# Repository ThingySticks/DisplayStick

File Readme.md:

Photon Display Prototyping PCB.
================================

Prototype board for Particle Photon with 3.2" (eBay) display with prototype area underneath.

See individual versions for PCB specifics.

[Available on Tindie](https://www.tindie.com/products/ThingySticks/display-stick-for-a-28-display-and-photon/)

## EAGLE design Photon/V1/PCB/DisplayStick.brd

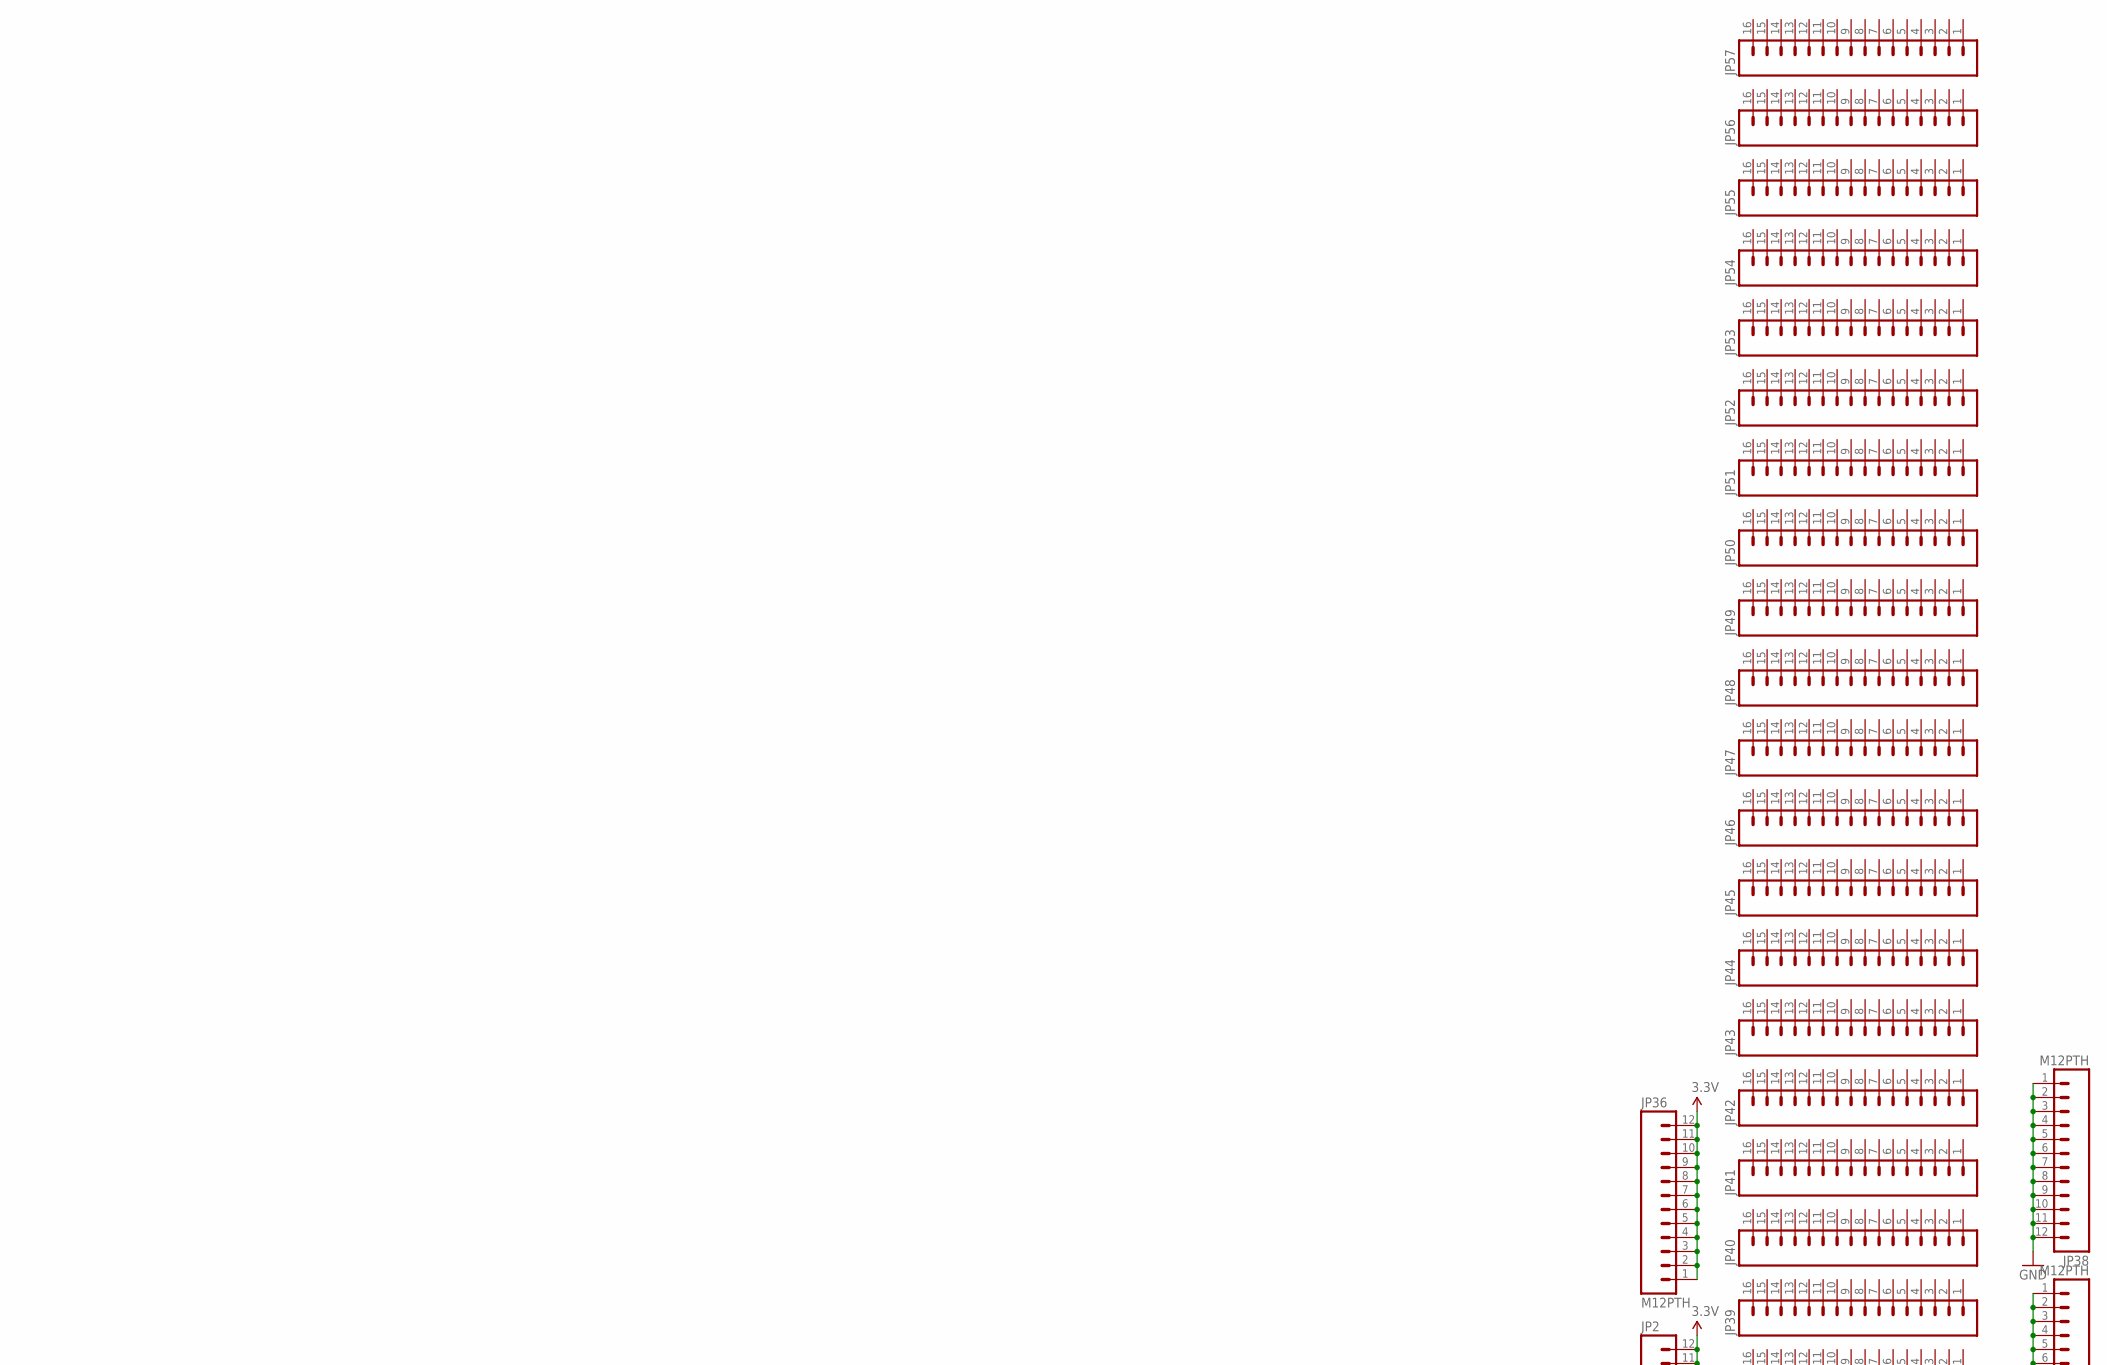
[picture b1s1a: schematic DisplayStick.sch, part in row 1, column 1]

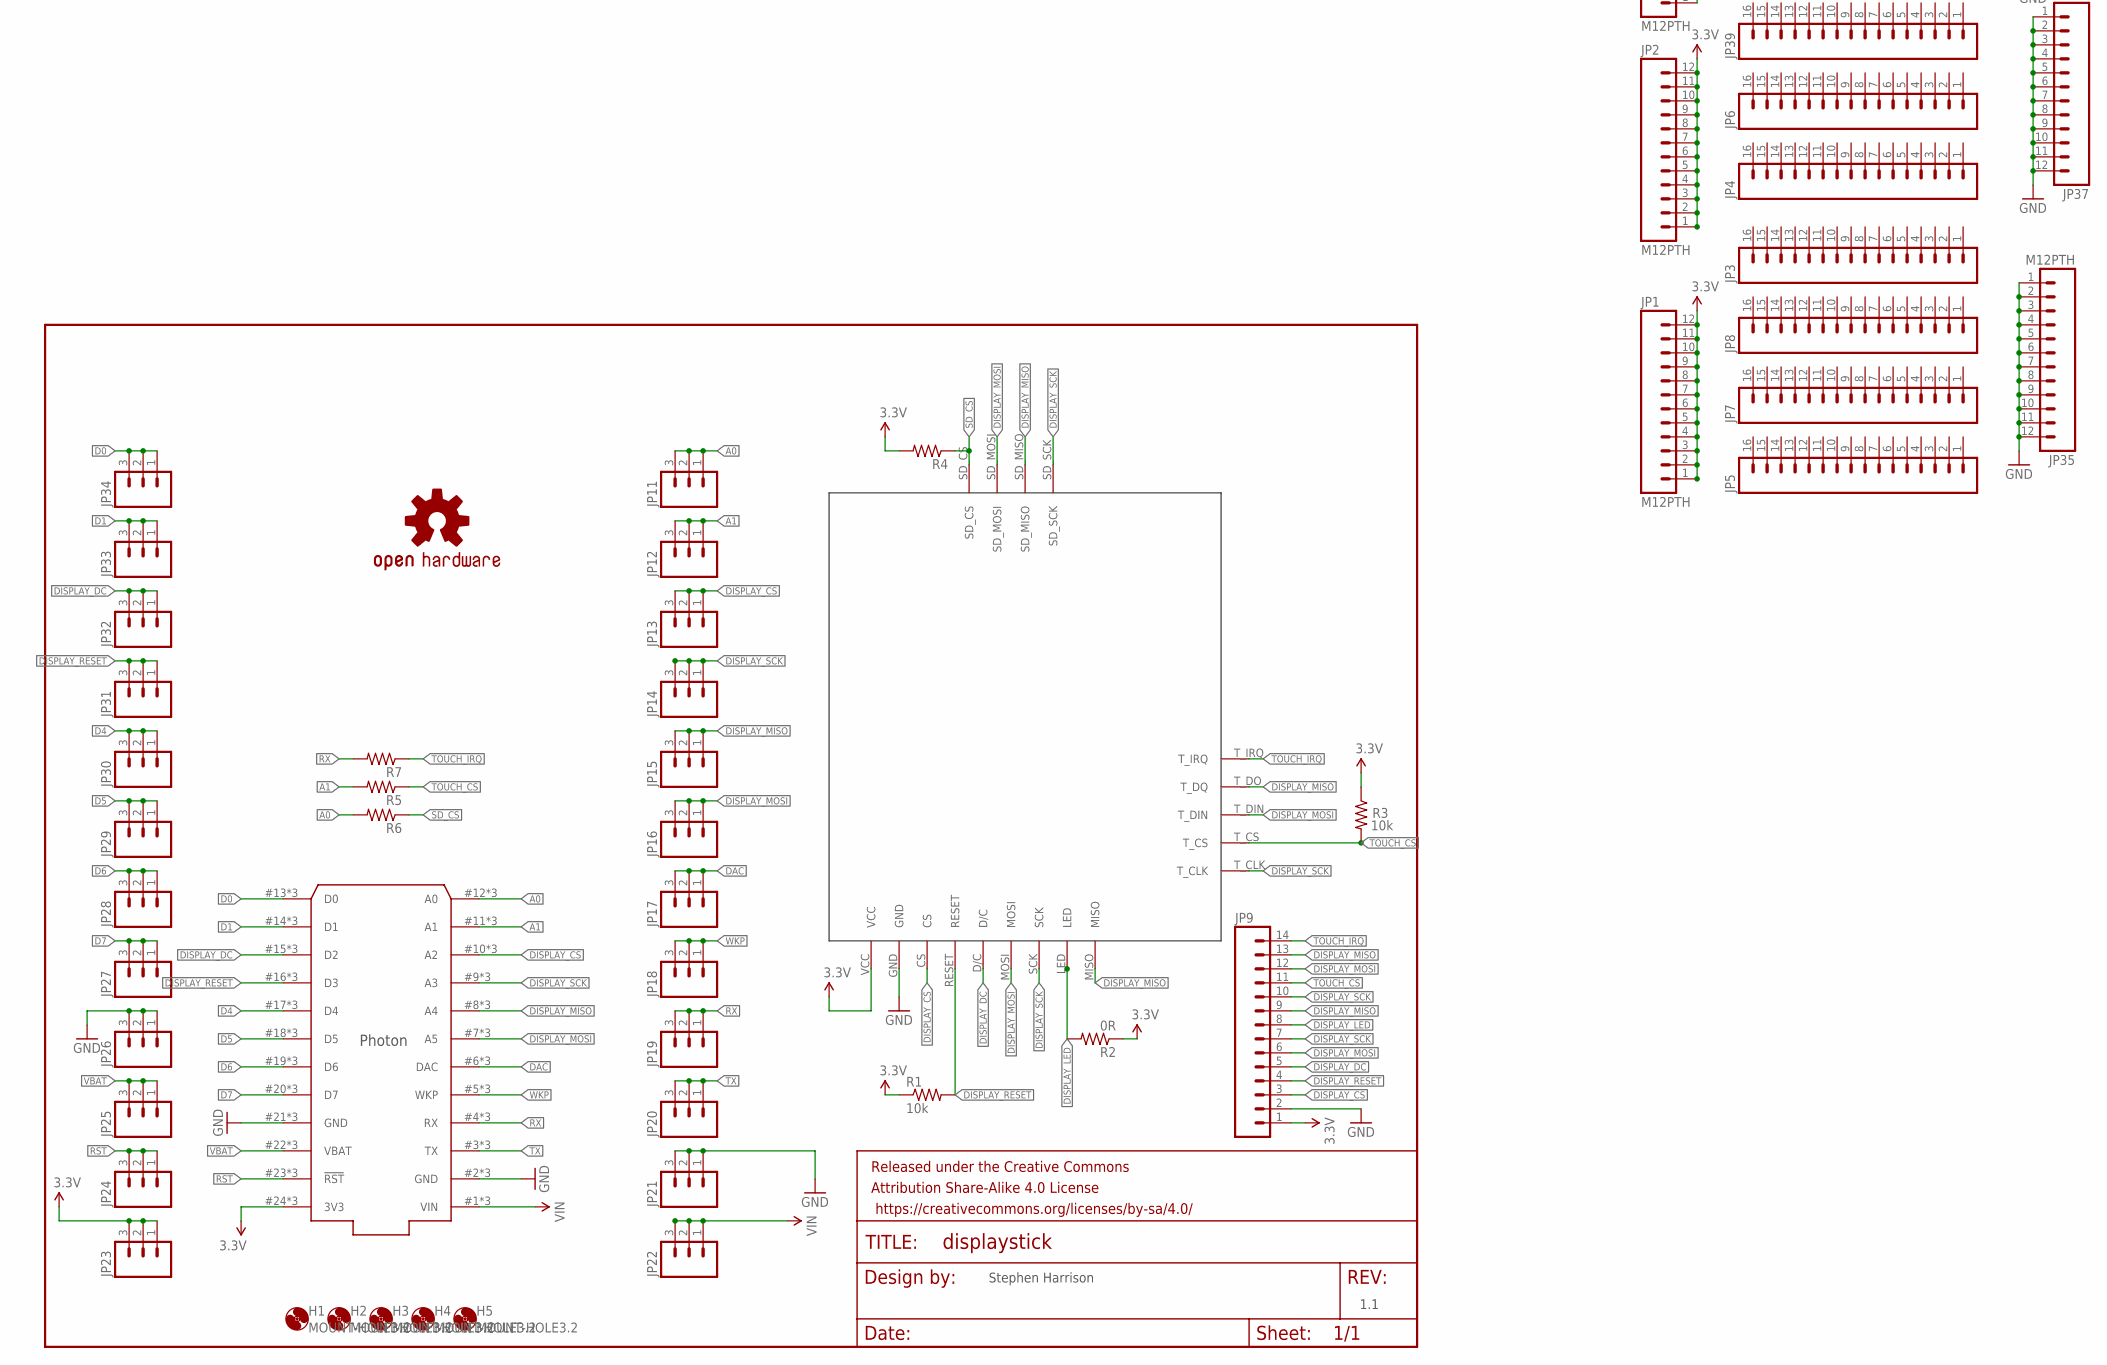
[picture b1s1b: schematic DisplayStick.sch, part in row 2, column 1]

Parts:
FRAME1: FRAME-LETTER; CREATIVE_COMMONS
H1, H2, H3, H4, H5: MOUNT-HOLE3.2; 3,2
JP1, JP2, JP35, JP36, JP37, JP38: M12PTH; 1X12-SMALL-PADS
JP3, JP4, JP5, JP6, JP7, JP8, JP39, JP40, JP41, JP42, JP43, JP44, JP45, JP46, JP47, JP48, JP49, JP50, JP51, JP52, JP53, JP54, JP55, JP56, JP57: M161X16_NO_SILK; 1X16_NO_SILK
JP9: M14; 1X14
JP11, JP12, JP13, JP14, JP15, JP16, JP17, JP18, JP19, JP20, JP21, JP22, JP23, JP24, JP25, JP26, JP27, JP28, JP29, JP30, JP31, JP32, JP33, JP34: M03PTH; 1X03
LOGO1: OSHW-LOGOL; OSHW-LOGO-L
R1, R3: 10k; 1206
R2: 0R; 1206
R4, R5, R6, R7: RESISTOR1206; 1206
U$1: TJCTM240
U$3: PHOTON_WITH_STACKABLE_HEADERS; PHOTON_STACKABLE

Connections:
3.3V: JP1.1, JP1.2, JP1.3, JP1.4, JP1.5, JP1.6, JP1.7, JP1.8, JP1.9, JP1.10, JP1.11, JP1.12, JP2.1, JP2.2, JP2.3, JP2.4, JP2.5, JP2.6, JP2.7, JP2.8, JP2.9, JP2.10, JP2.11, JP2.12, JP9.1, JP23.1, JP23.2, JP23.3, JP36.1, JP36.2, JP36.3, JP36.4, JP36.5, JP36.6, JP36.7, JP36.8, JP36.9, JP36.10, JP36.11, JP36.12, R1.1, R2.1, R3.1, R4.2, U$1.VCC, U$3.24 (3V3), U$3.#24 (3V3), U$3.@24 (3V3)
A0: JP11.1, JP11.2, JP11.3, R6.2, U$3.12 (A0), U$3.#12 (A0), U$3.@12 (A0)
A1: JP12.1, JP12.2, JP12.3, R5.2, U$3.11 (A1), U$3.#11 (A1), U$3.@11 (A1)
D0: JP34.1, JP34.2, JP34.3, U$3.13 (D0), U$3.#13 (D0), U$3.@13 (D0)
D1: JP33.1, JP33.2, JP33.3, U$3.14 (D1), U$3.#14 (D1), U$3.@14 (D1)
D4: JP30.1, JP30.2, JP30.3, U$3.17 (D4), U$3.#17 (D4), U$3.@17 (D4)
D5: JP29.1, JP29.2, JP29.3, U$3.18 (D5), U$3.#18 (D5), U$3.@18 (D5)
D6: JP28.1, JP28.2, JP28.3, U$3.19 (D6), U$3.#19 (D6), U$3.@19 (D6)
D7: JP27.1, JP27.2, JP27.3, U$3.20 (D7), U$3.#20 (D7), U$3.@20 (D7)
DAC: JP17.1, JP17.2, JP17.3, U$3.6 (DAC), U$3.#6 (DAC), U$3.@6 (DAC)
DISPLAY_CS: JP9.3, JP13.1, JP13.2, JP13.3, U$1.CS, U$3.10 (A2), U$3.#10 (A2), U$3.@10 (A2)
DISPLAY_DC: JP9.5, JP32.1, JP32.2, JP32.3, U$1.D/C, U$3.15 (D2), U$3.#15 (D2), U$3.@15 (D2)
DISPLAY_LED: JP9.8, R2.2, U$1.LED
DISPLAY_MISO: JP9.9, JP9.13, JP15.1, JP15.2, JP15.3, U$1.MISO, U$1.SD_MISO, U$1.T_DO (T_DQ), U$3.8 (A4), U$3.#8 (A4), U$3.@8 (A4)
DISPLAY_MOSI: JP9.6, JP9.12, JP16.1, JP16.2, JP16.3, U$1.MOSI, U$1.SD_MOSI, U$1.T_DIN, U$3.7 (A5), U$3.#7 (A5), U$3.@7 (A5)
DISPLAY_RESET: JP9.4, JP31.1, JP31.2, JP31.3, R1.2, U$1.RESET, U$3.16 (D3), U$3.#16 (D3), U$3.@16 (D3)
DISPLAY_SCK: JP9.7, JP9.10, JP14.1, JP14.2, JP14.3, U$1.SCK, U$1.SD_SCK, U$1.T_CLK, U$3.9 (A3), U$3.#9 (A3), U$3.@9 (A3)
GND: JP9.2, JP21.1, JP21.2, JP21.3, JP26.1, JP26.2, JP26.3, JP35.1, JP35.2, JP35.3, JP35.4, JP35.5, JP35.6, JP35.7, JP35.8, JP35.9, JP35.10, JP35.11, JP35.12, JP37.1, JP37.2, JP37.3, JP37.4, JP37.5, JP37.6, JP37.7, JP37.8, JP37.9, JP37.10, JP37.11, JP37.12, JP38.1, JP38.2, JP38.3, JP38.4, JP38.5, JP38.6, JP38.7, JP38.8, JP38.9, JP38.10, JP38.11, JP38.12, U$1.GND, U$3.2 (GND), U$3.21 (GND), U$3.#2 (GND), U$3.#21 (GND), U$3.@2 (GND), U$3.@21 (GND)
RST: JP24.1, JP24.2, JP24.3, U$3.23 (!RST), U$3.#23 (!RST), U$3.@23 (!RST)
RX: JP19.1, JP19.2, JP19.3, R7.2, U$3.4 (RX), U$3.#4 (RX), U$3.@4 (RX)
SD_CS: R4.1, R6.1, U$1.SD_CS
TOUCH_CS: JP9.11, R3.2, R5.1, U$1.T_CS
TOUCH_IRQ: JP9.14, R7.1, U$1.T_IRQ
TX: JP20.1, JP20.2, JP20.3, U$3.3 (TX), U$3.#3 (TX), U$3.@3 (TX)
VBAT: JP25.1, JP25.2, JP25.3, U$3.22 (VBAT), U$3.#22 (VBAT), U$3.@22 (VBAT)
VIN: JP22.1, JP22.2, JP22.3, U$3.1 (VIN), U$3.#1 (VIN), U$3.@1 (VIN)
WKP: JP18.1, JP18.2, JP18.3, U$3.5 (WKP), U$3.#5 (WKP), U$3.@5 (WKP)

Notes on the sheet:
1.1
Stephen Harrison

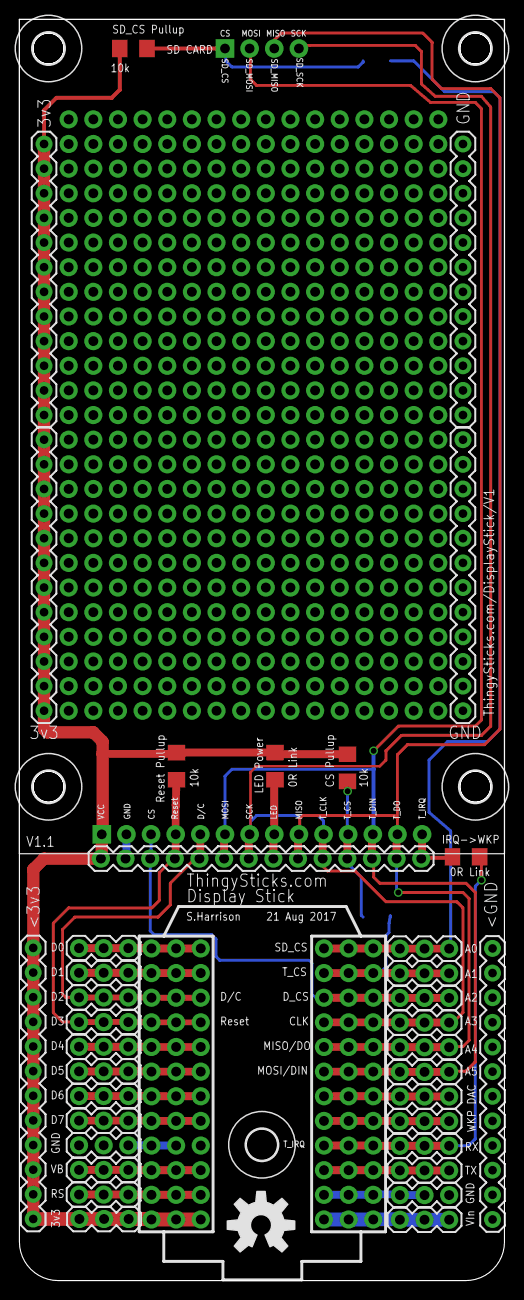
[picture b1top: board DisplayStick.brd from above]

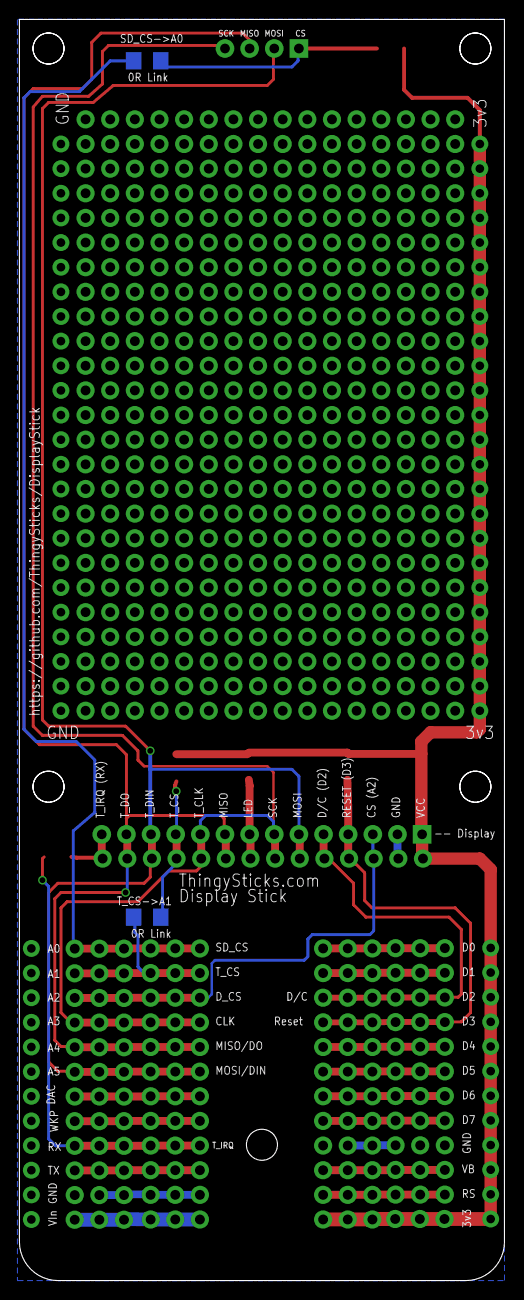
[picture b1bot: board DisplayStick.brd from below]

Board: 2 copper layers, 50.0 x 130.0 mm, 72 parts (2 on the bottom side), 27 nets.

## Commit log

2017-05-05 Initial version.
2017-08-21 Added links for touch and sd card chip selects. Removed upper J10 4 pin connector so it's more obvious which connector the display should go into.
    Bumped to V1.1
2017-11-26 Moved location of prototyping holes/connectors.
2017-11-26 Added PCB images.
2017-11-26 Work in progress case...
2017-11-27 Added Tindie link

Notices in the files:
parts and their libraries:
SparkFun-Aesthetics: Licensing: Creative Commons ShareAlike 4.0 International - https://creativecommons.org/licenses/by-sa/4.0
SparkFun-Aesthetics: Released under the Creative Commons Attribution Share-Alike 4.0 License
SparkFun-Aesthetics: https://creativecommons.org/licenses/by-sa/4.0
